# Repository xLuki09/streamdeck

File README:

A custom Macro Pad with 9 switches and a rotary encoder with buttonfunktion all controlled by an esp32 USB-C. Built on a custom PCB 
SOnn there will be a 3D modell for the casing and the source code

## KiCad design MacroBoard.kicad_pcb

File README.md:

# Streamdeck MacroPad

A custom, USB-C macro pad built around a Seeed Studio XIAO ESP32-C3. The current design has nine push buttons and a rotary encoder with a push-button function, all mounted on a custom PCB.

The goal is to make a compact, customizable input device for shortcuts such as launching apps or controlling common actions. This repository contains the KiCad design files, a Gerber and drill-file archive, board images, and the current parts list. The board has not been manufactured yet, and firmware is not included at this stage.

## Design

I started with a larger idea: twelve keys and a small OLED screen. I found that the extra controls made the wiring and PCB design too complicated for this first version, so I reduced the scope to nine keys and a rotary encoder. That gave me a more manageable design while keeping the controls I wanted for a useful macro pad.

I designed the schematic and PCB in KiCad. I later changed the controller to the smaller XIAO ESP32-C3, which provides a USB-C connector, and added labels to the PCB. The latest design check reported zero errors. A friend is going to review the board before I treat it as ready to manufacture.

## Current status

- **PCB design:** laid out in KiCad; the latest design check reported zero errors.
- **Manufacturing:** not ordered yet. I am sorting out the parts and hoping to get funding for the order.
- **Gerbers:** included in [`PCB/MacroBoardv3gerber.zip`](PCB/MacroBoardv3gerber.zip) for anyone who wants to inspect or reproduce the board. Please review the design and manufacturing files before ordering.
- **Enclosure:** in progress and not finished yet.
- **Firmware:** not available yet.

The design is still awaiting a second review, so the current files should be considered a pre-manufacturing version rather than a tested, finished device.

## Board images

### 3D board view

### PCB layout

## Parts list

The current estimated parts list is available as [BOM.csv](BOM.csv) and [BOM.md](BOM.md). The prices in the list are estimates and may change with supplier, shipping, and taxes. Check component footprints and quantities against the KiCad files before ordering.

## Building from the files

1. Open [`PCB/MacroBoard.kicad_sch`](PCB/MacroBoard.kicad_sch) or [`PCB/MacroBoard.kicad_pcb`](PCB/MacroBoard.kicad_pcb) in KiCad, then inspect the schematic and board layout.
2. Review the design and BOM, and confirm that the footprints and parts match the parts you plan to buy.
3. Use the Gerber and drill files in [`PCB/MacroBoardv3gerber.zip`](PCB/MacroBoardv3gerber.zip) to review or order the PCB.
4. Source the components, assemble and solder the board, then add firmware when it is available.

This project has not been assembled or tested as a working device yet. The Gerber archive is provided for reuse, but anyone reproducing the board should verify the files and design first.

## What I learned

Learning KiCad and turning the idea into a routed PCB took time. I learned how the schematic, footprints, PCB layout, and manufacturing files fit together. I also learned to reduce the feature set when the wiring and layout became too complicated: dropping the OLED and three keys made the first version more achievable.

One problem I ran into was that the 3D model did not link to its footprint correctly. That made me realize that a footprint and its 3D model need to be configured and checked together. I am still working through the enclosure design, and the board is waiting for another review before I order parts.

## Repository files

- [`PCB/MacroBoard.kicad_sch`](PCB/MacroBoard.kicad_sch) - schematic
- [`PCB/MacroBoard.kicad_pcb`](PCB/MacroBoard.kicad_pcb) - PCB layout
- [`PCB/MacroBoardv3gerber.zip`](PCB/MacroBoardv3gerber.zip) - Gerber and drill files
- [`BOM.csv`](BOM.csv) - spreadsheet-friendly parts list
- [`BOM.md`](BOM.md) - formatted parts list
- [`JOURNAL.md`](JOURNAL.md) - project development journal

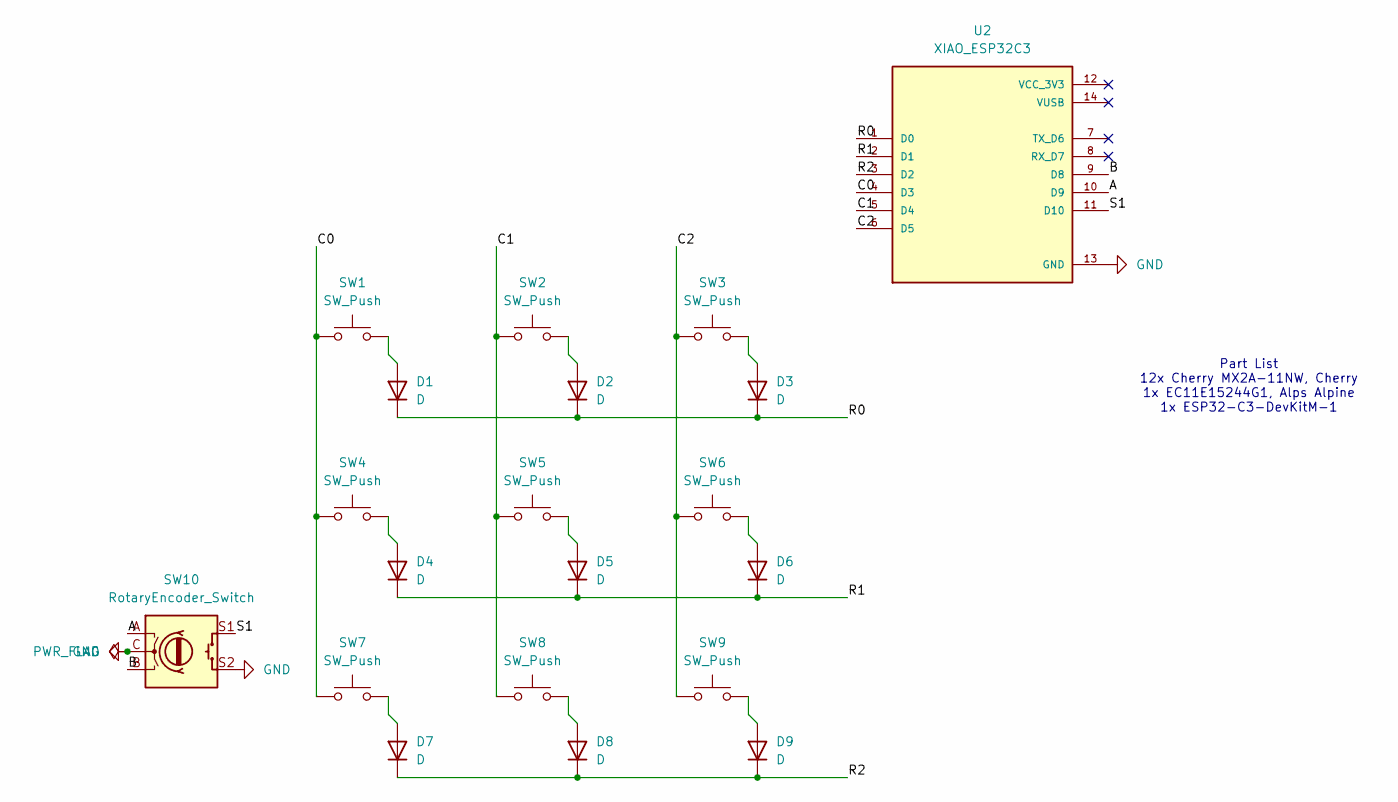
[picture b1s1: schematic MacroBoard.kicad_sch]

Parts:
D1, D2, D3, D4, D5, D6, D7, D8, D9: D; D_DO-35_SOD27_P7.62mm_Horizontal
SW1, SW2, SW3, SW4, SW5, SW6, SW7, SW8, SW9: SW_Push; SW_Cherry_MX_1.00u_PCB
SW10: RotaryEncoder_Switch; RotaryEncoder_Alps_EC11E-Switch_Vertical_H20mm
U2: XIAO_ESP32C3; MODULE_XIAO_ESP32C3; PARTREV 23/05/2022

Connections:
/A: SW10.A, U2.10 (D9)
/B: SW10.B, U2.9 (D8)
/C0: SW1.1, SW4.1, SW7.1, U2.4 (D3)
/C1: SW2.1, SW5.1, SW8.1, U2.5 (D4)
/C2: SW3.1, SW6.1, SW9.1, U2.6 (D5)
/R0: D1.1 (K), D2.1 (K), D3.1 (K), U2.1 (D0)
/R1: D4.1 (K), D5.1 (K), D6.1 (K), U2.2 (D1)
/R2: D7.1 (K), D8.1 (K), D9.1 (K), U2.3 (D2)
/S1: SW10.S1, U2.11 (D10)
GND: SW10.C, SW10.S2, U2.13 (GND)
unnamed: D1.2 (A), SW1.2
unnamed: D2.2 (A), SW2.2
unnamed: D3.2 (A), SW3.2
unnamed: D4.2 (A), SW4.2
unnamed: D5.2 (A), SW5.2
unnamed: D6.2 (A), SW6.2
unnamed: D7.2 (A), SW7.2
unnamed: D8.2 (A), SW8.2
unnamed: D9.2 (A), SW9.2

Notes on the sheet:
Part List 12x Cherry MX2A-11NW, Cherry 1x EC11E15244G1, Alps Alpine 1x ESP32-C3-DevKitM-1

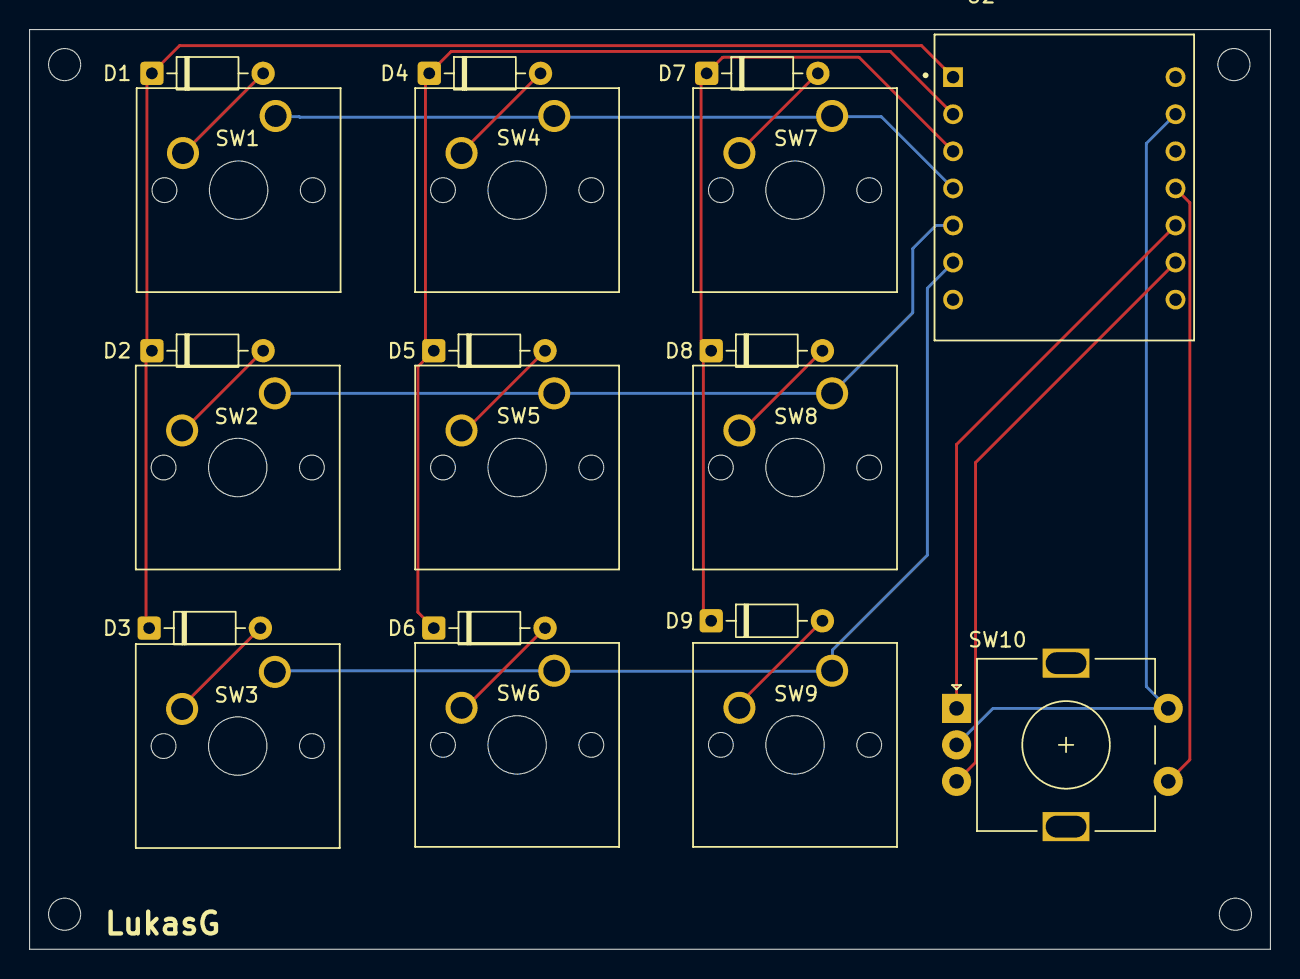
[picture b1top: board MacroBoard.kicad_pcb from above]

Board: 2 copper layers, 85.0 x 63.0 mm, 20 parts (0 on the bottom side), 19 nets.

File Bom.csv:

ID;Bezeichner;Footprint;Stückzahl;Bezeichnung;Anbieter und Referenz;
1;D1, D2, D3, D4, D5, D6, D7, D8, D9;D_DO-35_SOD27_P7.62mm_Horizontal;9;D;https://de.farnell.com/multicomp-pro/1n4148-do-35/kleinsigna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;
2;SW1, SW2, SW3, SW4, SW5, SW6, SW7, SW8, SW9;SW_Cherry_MX_1.00u_PCB;9;SW_Push;https://www.reichelt.com/de/en/shop/product/cherry_mx_red_ke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;
3;SW10;RotaryEncoder_Alps_EC11E-Switch_Vertical_H20mm;1;RotaryEncoder_Switch;https://www.mouser.at/de/ProductDetail/Same-Sky/RIC11-31S20D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;
4;U2;MODULE_XIAO_ESP32C3;1;XIAO_ESP32C3;https://www.tme.eu/en/details/seeed-113991054/development-ki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;
